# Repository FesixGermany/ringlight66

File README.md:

# ringlight66  

Ringlight for microscope with 16 LEDs running at 24V at 60-70mA in total (30-35mA per row of LEDs).  
Inner dia 47.2mm, outer dia 66mm.  

LEDs used are Nichia NFSW036DT which could be brighter with more current but I wanted to have more even illumination so I went with more LEDs at lower current instead of a few very bright ones at higher current. This also brings down the heat dissipation of the current limiting resistors and the LEDs.  

These LEDs are no longer available but others can be used with similar package such as PLCC-2. Forward voltage of LEDs will be different so the current limiting resistors might have to be changed.  
Also important to note is, that some LEDs have additional pads for heat dissipation in the middle. These would short the pads so such can not be used.

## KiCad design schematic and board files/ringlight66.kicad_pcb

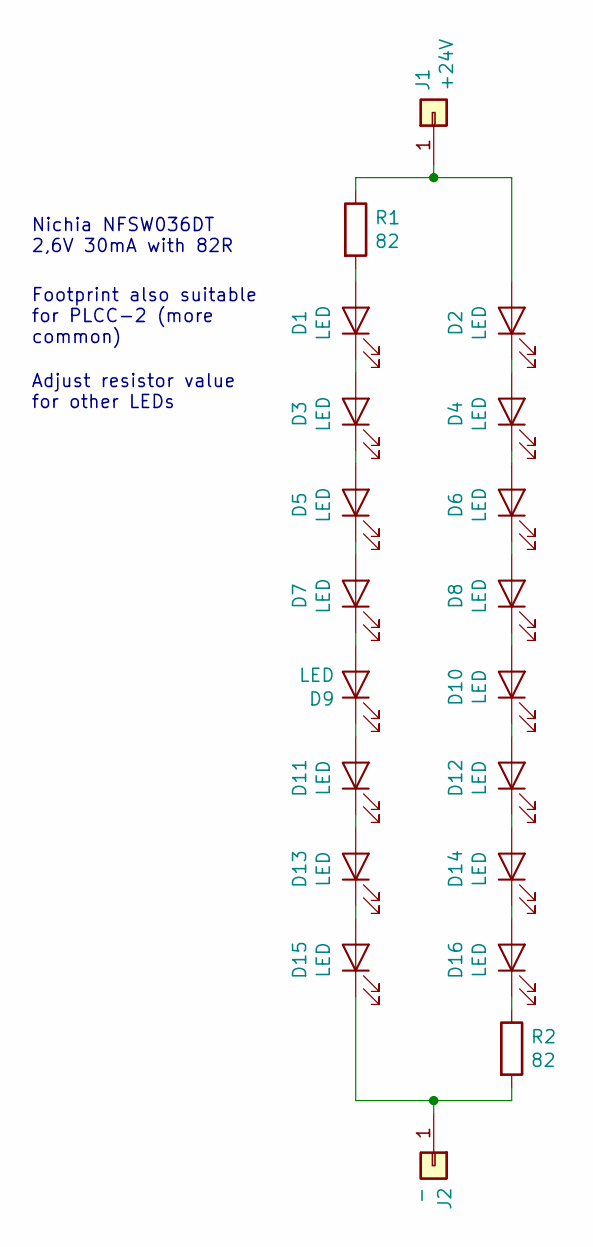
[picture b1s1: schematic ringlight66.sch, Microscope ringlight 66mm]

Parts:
D1, D2, D3, D4, D5, D6, D7, D8, D9, D10, D11, D12, D13, D14, D15, D16: LED; LED_3535
J1: +24V; SolderWirePad_1x01_SMD_5x10mm
J2: -; SolderWirePad_1x01_SMD_5x10mm
R1, R2: 82; R_1206_3216Metric_Pad1.42x1.75mm_HandSolder

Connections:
unnamed: D1.1 (K), D3.2 (A)
unnamed: D1.2 (A), R1.2
unnamed: D2.1 (K), D4.2 (A)
unnamed: D2.2 (A), J1.1, R1.1
unnamed: D3.1 (K), D5.2 (A)
unnamed: D4.1 (K), D6.2 (A)
unnamed: D5.1 (K), D7.2 (A)
unnamed: D6.1 (K), D8.2 (A)
unnamed: D7.1 (K), D9.2 (A)
unnamed: D10.1 (K), D12.2 (A)
unnamed: D8.1 (K), D10.2 (A)
unnamed: D11.1 (K), D13.2 (A)
unnamed: D9.1 (K), D11.2 (A)
unnamed: D12.1 (K), D14.2 (A)
unnamed: D13.1 (K), D15.2 (A)
unnamed: D14.1 (K), D16.2 (A)
unnamed: D15.1 (K), J2.1, R2.2
unnamed: D16.1 (K), R2.1

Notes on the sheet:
Nichia NFSW036DT 2,6V 30mA with 82R
Footprint also suitable for PLCC-2 (more common)
Adjust resistor value for other LEDs

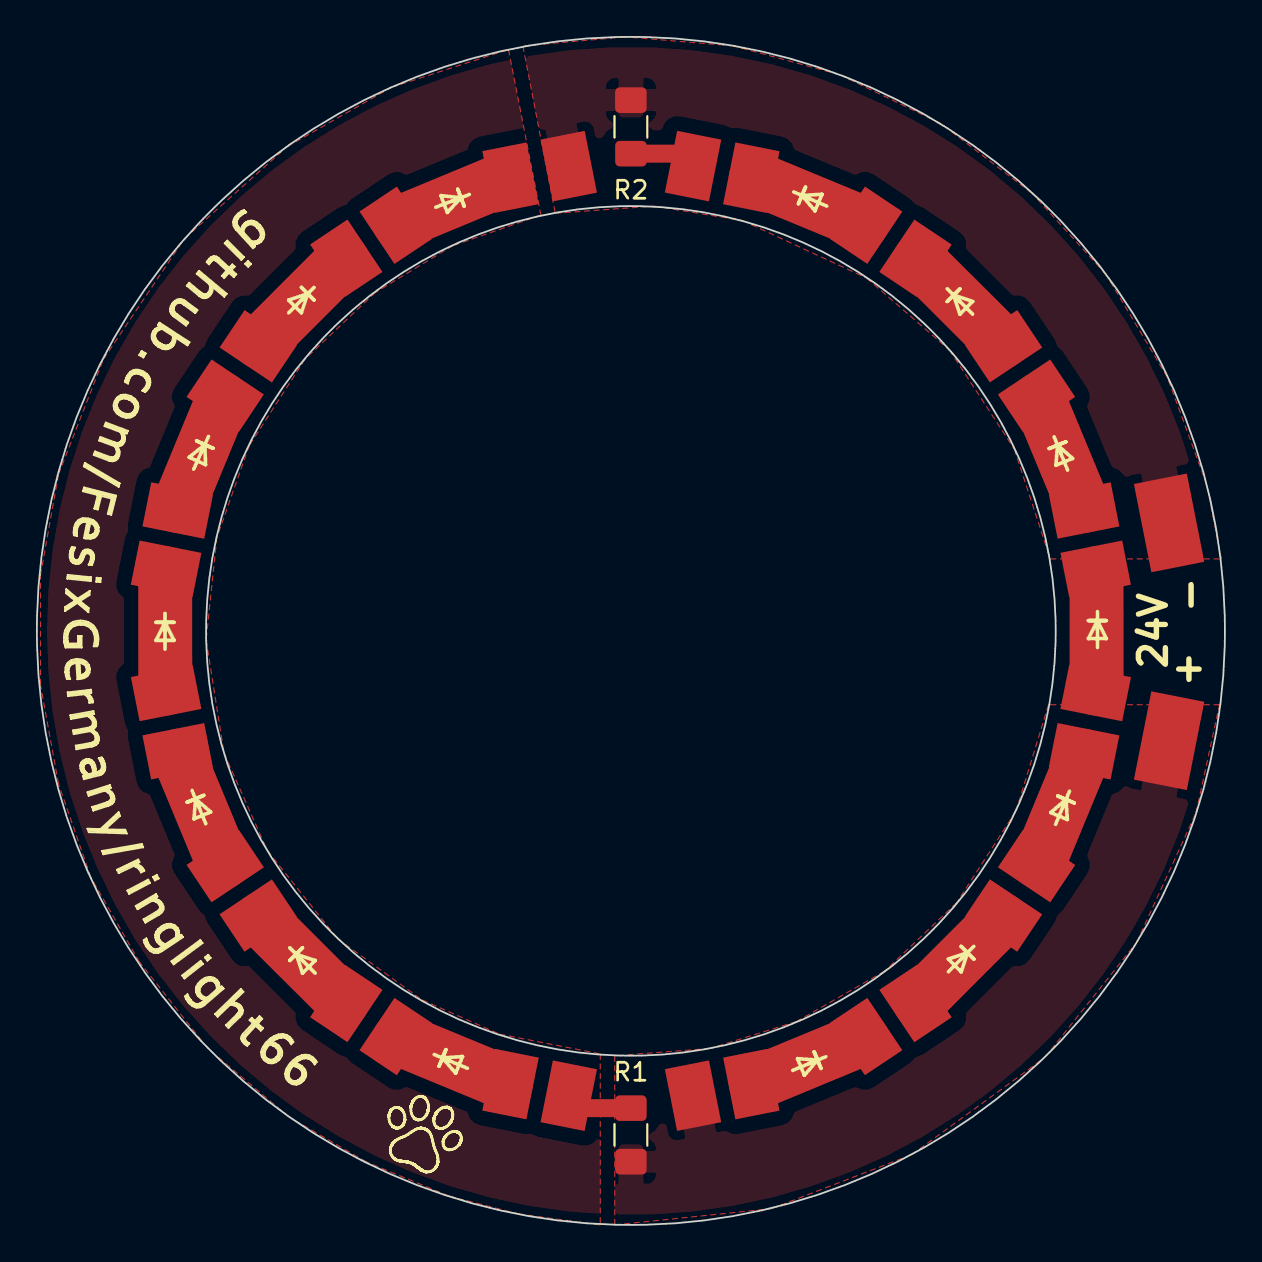
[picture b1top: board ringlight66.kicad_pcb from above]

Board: 2 copper layers, 66.0 x 66.0 mm, 20 parts (0 on the bottom side), 18 nets.

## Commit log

2021-02-28 initial
